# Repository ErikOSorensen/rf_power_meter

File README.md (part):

# RF Power Meter

Dual-channel RF power meter using Raspberry Pi Pico with W5500 Ethernet, featuring SCPI control and mDNS discovery.

## Architecture Overview

```
┌─────────────────────────────────────────────────────────────────┐
│                         main.py                                  │
│                    (Application Controller)                      │
│  - Initializes all subsystems                                   │
│  - Runs async task scheduler                                    │
│  - Coordinates sensor reading, display, and network tasks       │
└─────────────────────────────────────────────────────────────────┘
         │              │              │              │
         ▼              ▼              ▼              ▼
┌─────────────┐ ┌─────────────┐ ┌─────────────┐ ┌─────────────┐
│   sensors/  │ │  display/   │ │    net/     │ │    scpi/    │
│             │ │             │ │             │ │             │
│ Head ADC,   │ │ 256x64 OLED │ │ Ethernet &  │ │  Command    │
│ temp, EEPROM│ │ both chans  │ │ TCP server  │ │  parsing    │
└─────────────┘ └─────────────┘ └─────────────┘ └─────────────┘
```

## Key Features

- **EEPROM-based calibration**: Each sensor module stores its own calibration data in an onboard EEPROM. Calibration travels with the sensor, not the channel.
- **Frequency-dependent calibration**: Store separate offset/slope corrections for each calibration frequency. Between points the corrections are linearly interpolated.
- **Self-contained sensor heads**: Each head carries its detector, 16-bit ADC, temperature sensor and EEPROM. Only power and I2C travel over the cable.
- **One I2C bus per head**: Each sensor head hangs on its own Pico I2C controller (I2C0 for channel 1, I2C1 for channel 2), so heads are interchangeable and no multiplexer is needed.
- **Hot-swappable sensors**: Sensors are automatically detected at startup and on plug-in via a presence detect line.
- **Single 256x64 grayscale OLED**: An SSD1322 panel over SPI shows both channels, one row each.
- **Front panel encoder**: A rotary encoder with push switch sets the frequency and external attenuator of each channel. SCPI writes override it, and `SYSTem:KLOCk` can lock it out.
- **SCPI control**: Standard SCPI commands over TCP port 5025.
- **mDNS discovery**: Find the meter as `rfmeter.local`.

## Display

The main screen, rendered at 3x by `python3 tests/test_screen.py docs/display_main.png 3`
with the firmware's own layout code (`src/display/layout.py`).

## Repository Layout

| Directory | Contents |
|-----------|----------|
| `src/` | MicroPython firmware. Its contents mirror the Pico's filesystem root: everything in it, and nothing else, is copied to the Pico. |
| `tools/` | Desktop-only Python scripts (font generation, calibration, test utilities). Never copied to the Pico. See `tools/README.md`. `tools/sim/` holds desktop stand-ins for MicroPython modules (`framebuf`, `micropython`). |
| `tests/` | Tests that run both on the Pico (`mpremote run`) and on the desktop. `tests/test_screen.py` renders the display screens to PNG. |
| `docs/` | Images for the documentation, such as the display render above. |
| `hardware/` | KiCad projects and the project-local KiCad library. See `hardware/README.md`. |

### Deploying the Firmware

With [`mpremote`](https://docs.micropython.org/en/latest/reference/mpremote.html):

```
cd src
mpremote cp -r . :
mpremote reset
```

## File Responsibilities

All paths below are relative to `src/`.

### Core

| File | Purpose |
|------|---------|
| `main.py` | Application entry point. Initializes hardware, detects sensors, starts async tasks for sensor reading (50ms), display updates (200ms), TCP server, and mDNS. |
| `config.py` | Central configuration: GPIO pins, I2C buses and addresses, display SPI, encoder, network settings, instrument identity. |

### Sensors (`sensors/`)

| File | Purpose |
|------|---------|
| `ads1115.py` | Low-level driver for the ADS1115 16-bit ADC in each sensor head. Continuous-conversion mode; reads never block. |
| `mcp9808.py` | Driver for the MCP9808 temperature sensor in each sensor head. |
| `eeprom.py` | AT24Cxx EEPROM driver. Reads/writes sensor type, serial number, and calibration data. |
| `calibration.py` | Calibration management. Holds the per-channel I2C buses, detects sensors via EEPROM, manages per-frequency calibration, handles voltage-to-dBm conversion. |
| `power_sensor.py` | High-level power measurement. `PowerChannel` handles per-channel reading and averaging. `PowerMeter` manages both channels. |

### Display (`display/`)

| File | Purpose |
|------|---------|
| `ssd1322.py` | Low-level driver for the SSD1322 256x64 4-bit grayscale OLED (4-wire SPI). Frame buffer is `framebuf.GS4_HMSB`, which matches the controller's RAM layout. |
| `bitmapfont.py` | Draws the generated bitmap fonts in `fonts/` (B612 Bold 30 px, Regular 12 px and 9 px; 4-bit antialiased, tabular digits). Regenerate with `tools/fonts/make_fonts.py`. |
| `layout.py` | Screen layout, hardware-free so it also runs on the desktop. One 32 px row per channel: channel name with sensor type and head temperature, frequency and pad (editable, inverted while editing), the reading in 30 px B612 Bold right-aligned at a fixed position, and the unit. Also the startup (IP address, hostname), error and remote-lock screens. |
| `power_display.py` | `DisplayManager`: owns the panel, reads the meter state and draws it with `layout.py`. Holds the startup screen with the IP address for 3 s after DHCP succeeds. |

### Front Panel (`ui/`)

| File | Purpose |
|------|---------|
| `encoder.py` | Rotary encoder quadrature decoder and push button, interrupt driven. Expects hardware-debounced inputs. |
| `front_panel.py` | Edit-mode state machine: short press cycles CH1 frequency → CH1 attenuator → CH2 frequency → CH2 attenuator → back to measurement; rotation changes the highlighted value; 5 s idle timeout; remote lock. |

### Network (`net/`)

| File | Purpose |
|------|---------|
| `w5500.py` | W5500 Ethernet initialization. Configures SPI, handles DHCP. |
| `tcp_server.py` | Async TCP server on port 5025 (SCPI standard). |
| `mdns.py` | Multicast DNS responder. Announces `rfmeter.local`. |

### SCPI (`scpi/`)

| File | Purpose |
|------|---------|
| `parser.py` | SCPI command parser. Handles short/long form matching. |
| `commands.py` | SCPI command implementations. |

## Hardware Design

### Design Principle: Digital-Only Cable

Each sensor head contains the complete analog signal chain: RF detector,
RC filter and a 16-bit ADS1115 ADC. The head also carries an EEPROM
(identity and calibration) and an MCP9808 temperature sensor next to the
detector, plus its own voltage regulators. The cable to the main unit
carries only an 8V supply rail, I2C and a presence line.

This keeps the detector's millivolt-level output off the cable, so cable
length, connector contact resistance and ground offsets between units no
longer affect the reading.

### System Block Diagram

```
┌──────────────────────────────────┐              ┌──────────────────────────────┐
│ Sensor Head 1                    │              │       Main Unit (Pico)       │
│                                  │              │                              │
│  RF IN   ┌─────────┐  ┌────────┐ │   Ethernet   │     ┌──────────────────┐     │
│  (SMA) ──┤ AD8307  ├─►│ADS1115 ├─┤   cable      │     │       Pico       │     │
│          └─────────┘  │  0x48  │ │ (8V + I2C)   │     │                  │     │
│          ┌─────────┐  └────────┤ │              │     │ I2C0 (GP0/GP1)   │     │
│          │ MCP9808 ├───────────┼─┼══════════════┼─────┤                  │     │
│          │  0x18   │  ┌────────┤ │              │     │ I2C1 (GP2/GP3)   │     │
│          └─────────┘  │ EEPROM │ │              │  ┌──┤                  │     │
│                       │  0x50  │ │              │  │  │ SPI0 (GP16-19)   ├──┐  │
│                       └────────┘ │              │  │  │ SPI1 (GP10/11)   ├┐ │  │
└──────────────────────────────────┘              │  │  └──────────────────┘│ │  │
                                                  │  │                      │ │  │
┌──────────────────────────────────┐              │  │  ┌───────────────┐   │ │  │
│ Sensor Head 2                    │              │  │  │  SSD1322 OLED │◄──┘ │  │
│                                  │              │  │  │  256 x 64     │     │  │
│  RF IN   ┌─────────┐  ┌────────┐ │   Ethernet   │  │  └───────────────┘     │  │
│  (SMA) ──┤ AD8318  ├─►│ADS1115 ├─┤   cable      │  │  ┌───────────────┐     │  │
│          └─────────┘  │  0x48  │ │ (8V + I2C)   │  │  │     W5500     │◄────┘  │
│          ┌─────────┐  └────────┤ │              │  │  │   Ethernet    │        │
│          │ MCP9808 ├───────────┼─┼══════════════┼──┘  └───────────────┘        │
│          │  0x18   │  ┌────────┤ │              │                              │
│          └─────────┘  │ EEPROM │ │              │                              │
│                       │  0x50  │ │              │                              │
│                       └────────┘ │              │                              │
└──────────────────────────────────┘              └──────────────────────────────┘
```

Every head uses the same I2C addresses, so the heads are interchangeable.
The RP2040 has two independent I2C controllers; each one is wired to one
RJ45 jack, so head 1 is always on I2C0 and head 2 on I2C1. Nothing else
shares those buses.

### Ethernet Cable Pinout (T-568B)

Sensors connect to the main unit via standard Ethernet cables. Only power
and digital signals are carried.

Each I2C line shares a twisted pair with its own ground return, which
keeps SDA-to-SCL crosstalk low and gives each signal a tight return path.

| Pin | Pair | Wire Color | Function | Notes |
|-----|------|------------|----------|-------|
| 1 | Orange | Orange/White | V+ (8V) | Head supply from the main unit's LM317, 12V TVS per port |
| 2 | Orange | Orange | GND | Power return |
| 3 | Green | Green/White | I2C SDA | Pico I2C0 (head 1) or I2C1 (head 2) |
| 6 | Green | Green | GND | Return for SDA |
| 4 | Blue | Blue | I2C SCL | Pico I2C0 (head 1) or I2C1 (head 2) |
| 5 | Blue | Blue/White | GND | Return for SCL |
| 7 | Brown | Brown/White | GND | Return for presence detect |
| 8 | Brown | Brown | Presence Detect | Tied to GND in the head; pulled up in the main unit |

**Power Supply Notes:**
- The cable carries a single V+ of 8V, made by an LM317 on the main
  board. Each head still regulates its own 3.3V (and 5V where the
  detector needs it), so cable drop, contact resistance and main-unit
  supply noise do not reach the analog parts.
- The EEPROM, ADS1115 and MCP9808 always run on the head's 3.3V
- 3.3V detectors (AD8307, LTC5582): detector VCC from the head's 3.3V LDO
- 5V detectors (AD8317, AD8318): detector VCC from the head's 5V LDO
- Pins 2, 5, 6 and 7 are all GND and tied together at both ends; no
  conductor in the cable floats

**Hot-Swap Detection:**
- Pin 8 is tied to GND in each sensor head
- Main unit pulls each presence detect GPIO up to 3.3V (10kΩ, plus the
  RP2040 internal pull-up)
- When sensor is connected: GPIO reads LOW
- When sensor is disconnected: GPIO reads HIGH
- Either edge triggers sensor re-detection, which also re-configures the
  head's ADC (it powers up in single-shot mode)
- A ground tie needs no working rail in the head, so a head with a dead
  regulator still registers as present and can be reported as faulty

### I2C Topology

The main unit has no I2C devices of its own. Each of the Pico's two
I2C controllers runs straight to one RJ45 jack:

| Pico bus | Pins | Goes to |
|----------|------|---------|
| I2C0 | GP0 (SDA), GP1 (SCL) | RJ45 #1, sensor head 1 |
| I2C1 | GP2 (SDA), GP3 (SCL) | RJ45 #2, sensor head 2 |

**Sensor head bus (identical in every head):**

| Device | Address | Function |
|--------|---------|----------|
| ADS1115 | 0x48 | ADC for detector output (ADDR → GND) |
| MCP9808 | 0x18 | Temperature next to the detector (A0-A2 → GND) |
| AT24CS04 | 0x50 (0x51 upper half, 0x58 factory serial) | Sensor type, serial number, calibration |

Because the heads never share a bus, there is no multiplexer and no
channel-select transaction. A fault on one cable (a head yanked
mid-transfer, a shorted SDA) can only hang that channel's bus; the other
channel and the display are unaffected.

**Why One ADS1115 Per Head?**

1. **No analog on the cable**: The detector output is digitised within a
   few centimetres of the detector.
2. **Interchangeable heads**: Every head looks the same to the main unit.
   Calibration, identity and ADC travel together.
3. **Independent sampling**: Both ADCs free-run in continuous mode at
   128 SPS on separate buses. The Pico just reads the latest conversion
   from each head, so reads do not block and the two channels are
   sampled within a millisecond of each other.
4. **Spare inputs**: AIN2/AIN3 (grounded on the AD8307 head) are available for future heads with two
   detectors (e.g. a directional coupler head reporting forward and
   reflected power).

**Why a Temperature Sensor in the Head?**

Logarithmic detectors drift with temperature (AD8307: roughly ±0.3 dB
over -40 to +85 °C, AD8318 somewhat more). Measuring the temperature
at the detector allows this drift to be characterised per head and
compensated in firmware. The reading is available via
`MEASure:TEMPerature[1|2]?`. Temperature compensation coefficients are
not yet stored in the EEPROM format (see format version in `src/sensors/eeprom.py`).

### Pico Pin Assignments

| Function | Pico Pin | Notes |
|----------|----------|-------|
| Head 1 I2C SDA | GP0 | I2C0 → RJ45 #1 pin 3 |
| Head 1 I2C SCL | GP1 | I2C0 → RJ45 #1 pin 4 |
| Head 2 I2C SDA | GP2 | I2C1 → RJ45 #2 pin 3 |
| Head 2 I2C SCL | GP3 | I2C1 → RJ45 #2 pin 4 |
| Sensor 1 Detect | GP4 | Pull-up, active low, IRQ on edge |
| Sensor 2 Detect | GP5 | Pull-up, active low, IRQ on edge |
| Encoder A | GP6 | Via RC filter + 74HC14, IRQ on edge |
| Encoder B | GP7 | Via RC filter + 74HC14, IRQ on edge |
| Encoder Switch | GP8 | Via RC filter + 74HC14, high = pressed |
| Display SPI SCK | GP10 | SPI1 |
| Display SPI MOSI | GP11 | SPI1 TX (SSD1322 is write-only) |
| Display CS | GP13 | Active low |
| Display D/C | GP14 | High = data, low = command |
| Display RST | GP15 | Active low |
| W5500 SPI MISO | GP16 | SPI0 |
| W5500 CS | GP17 | |
| W5500 SPI SCK | GP18 | SPI0 |
| W5500 SPI MOSI | GP19 | SPI0 |
| W5500 RST | GP20 | |
| W5500 INT | GP21 | Not used by the firmware |

The controller is a W5500-EVB-Pico, so the W5500 and its SPI wiring
(GP16-GP21) are on the module itself. GP9, GP12, GP22 and GP26-GP28 are
free (extra buttons, status LED).

### Sensor Head Schematic

Each sensor head contains an RF detector, an ADS1115 ADC, an MCP9808
temperature sensor, an EEPROM and its own voltage regulation. The cable
delivers 8V; the head makes a 3.3V rail for the digital parts and, for
5V detectors, a 5V rail as well.

```
                 ┌──────────────────────────────────────────────────────────────────┐
                 │                          Sensor Head                             │
   RJ45          │                                                                  │
  ┌─────┐        │  ┌─────┐  ┌───────────┐   5V (detector)   ┌───────────┐          │
  │1 V+ ├────────┼──┤ TVS ├──┤ 5V LDO    ├───────────────────┤ 3.3V LDO  ├──┬─ 3V3  │
  │2 GND├────────┼┐ │10µF │  │ 5V heads  │                   │           │  │       │
  │3 SDA├────┐   ││ └─────┘  └───────────┘                   └───────────┘  │       │
  │6 GND├────┼───┼┤     (3.3V heads: V+ feeds the 3.3V LDO directly)        │       │
  │4 SCL├────┼─┐ ││                                                         │       │
  │5 GND├────┼─┼─┼┤                                                         │       │
  │7 GND├────┼─┼─┼┤   ┌──────────┐  ┌──────────┐     ┌──────────┐           │       │
  │8 DET├─┐  │ │ ││   │ ADS1115  │  │ MCP9808  │     │ EEPROM   │           │       │
  └─────┘ │  │ │ ││   │  0x48    ├──┤  0x18    ├─────┤  0x50    ├───────────┘       │
         GND │ │ ││   │ SDA  SCL │  │ SDA  SCL │     │ SDA  SCL │  (all on 3V3)     │
             │ │ ││   └──┬────┬──┘  └──┬────┬──┘     └──┬────┬──┘                   │
             └─┼─┼┼──────┴────┼────────┴────┼───────────┴────┼──── SDA  [4.7k → 3V3] │
               └─┼┼───────────┴─────────────┴────────────────┴──── SCL  [4.7k → 3V3] │
                 ││                                                                  │
                 ││   ADS1115 AIN0 ◄──────────┬── OUT  ┌─────────────┐              │
                 ││                        [100nF]     │ RF Detector │              │
                 ││   ADS1115 AIN1 ◄──────────┴── COM  │   AD8307    ├─[3dB pad]─ SMA│
                 ││                                    │ VCC ◄───────┼── 3V3 or 5V   │
                 │└─ GND                               └─────────────┘   rail        │
                 │                                                                  │
                 │   ADS1115: ADDR → GND, ALERT/RDY → 10kΩ pull-up, AIN2/AIN3 → GND  │
                 └──────────────────────────────────────────────────────────────────┘
```

**Component List (per sensor head):**
- RF detector IC (AD8307, AD8317, AD8318, LTC5582, etc.)
- ADS1115 16-bit ADC (TSSOP-10), ADDR → GND
- MCP9808 temperature sensor (MSOP-8), A0-A2 → GND, placed as close to the detector as layout allows
- AT24CS04-SSHM EEPROM, SOIC-8 (I2C address 0x50, factory serial number at 0x58; A1, A2 and WP → GND)
- 3.3V low-noise LDO LP2985-33 (SOT-23-5, 16V input; MIC5205-3.3 is a drop-in alternative) for ADC, temperature sensor, EEPROM and 3.3V detectors
- 5V LDO (e.g. AP7361C-50 or LD1117S50, SOT-223) on 5V-detector heads only; the 3.3V LDO then cascades from the 5V rail
- Power input: 10µF/25V tantalum + 12V TVS (SMF12A) on V+; LP2985 with 1µF at VIN, 10nF on BYPASS and 10µF tantalum at VOUT
- RJ45 jack: Würth 615108150221R mid-mount (shielded, tab down, no magnetics, no LEDs; project library `rf_power_meter:RJ45_WE-615108150221R`), sits in a board-edge cutout to fit the enclosure height; pin 8 tied to GND for presence detect
- SMA connector for RF input: Amphenol RF 132289, edge mount (project library `rf_power_meter:SMA_132289`)
- 3 dB pi attenuator between SMA and detector: 17.6Ω series, 2× 294Ω shunt, thin-film 1% (see `hardware/README.md`)
- Detector output filter: 100nF from OUT to ground, straight into ADS1115 AIN0 (the AD8307 output is 12.5kΩ, no series resistor needed)
- Detector input network: 52.3Ω termination, 2× 10nF C0G coupling capacitors on INP and INM (see `hardware/README.md`)
- Decoupling capacitors (100nF on each IC supply pin)
- I2C pull-up resistors (2× 4.7kΩ to the head's 3V3)
- 10kΩ pull-up on ADS1115 ALERT/RDY (unused, keeps the open-drain output defined)
- ESD protection (1× ESDAVLC6-2BLY for I2C lines)
- RF detector support components (per datasheet)

**Board markings:** the head PCB silkscreen carries the I2C address
table (ADS1115 0x48, MCP9808 0x18, AT24CS04 0x50 lower / 0x51 upper) and
the head label on the top side, and the RJ45 pinout on the bottom side,
so a head can be checked on the bench without this document.

**Test points:** six beaded wire loops (TestPoint_Loop_D1.80mm, 1.0 mm
hole) for bench checks: TP1 detector output (AD8307 OUT / ADS1115
AIN0), TP2 +3V3, TP3 VCC (the 8 V from the cable), TP4 SDA, TP5 SCL,
TP6 GND. Clip a scope ground to TP6 and the detector output can be
watched live while the ADC reads it.

**Detector Supply Voltage Reference:**

| Sensor | Supply | Head rail for detector | Max output | Fits ADS1115 at 3.3V? |
|--------|--------|------------------------|------------|------------------------|
| AD8307 | 2.7V - 5.5V | 3.3V (5V optional) | ~2.5V | Yes |
| AD8317 | 3.0V - 5.5V | 5V recommended | ~2.1V | Yes |
| AD8318 | 4.5V - 5.5V | 5V required | ~2.1V | Yes |
| LTC5582 | 3.0V - 3.6V | 3.3V only | ~2.1V | Yes |

The ADS1115 runs from 3.3V in all heads. Its inputs must stay below
VDD + 0.3V, which every listed detector satisfies even when powered from 5V.
The PGA is set to ±4.096V (125 µV/LSB); for a detector with a 25 mV/dB
slope that is 0.005 dB per count.

### Main Unit Schematic

The main unit takes 12V DC from a 1A adapter. Three regulators make the
rails: an LM317 (SOT-223) set to 8V for the two RJ45 ports (12V TVS per port), a 5V
buck module for the W5500-EVB-Pico, whose own 3.3V regulator powers the
RP2040 and the W5500, and a small 3.3V LDO for the OLED module. With the
analog chain moved to the heads, the main unit is purely digital.

```
  12V DC ───┬──► LM317 (8V) ──────────────────────────────────► To RJ45 Pin 1 (V+)
            │                                                     via 12V TVS per port
            ├──► 5V buck module ───────┬──► Pico VSYS (RP2040 + W5500)
            │                          └──► 3.3V LDO ──► OLED module
            │
            │    Raspberry Pi Pico
            │   ┌─────────────────┐
            │   │ GP0 (I2C0 SDA)  ├──[10kΩ to 3V3]──► RJ45 #1 pin 3 (SDA)
            │   │ GP1 (I2C0 SCL)  ├──[10kΩ to 3V3]──► RJ45 #1 pin 4 (SCL)
            │   │ GP2 (I2C1 SDA)  ├──[10kΩ to 3V3]──► RJ45 #2 pin 3 (SDA)
            │   │ GP3 (I2C1 SCL)  ├──[10kΩ to 3V3]──► RJ45 #2 pin 4 (SCL)
            │   │ GP4 (DET1)      ├◄─[10kΩ to 3V3]─── RJ45 #1 pin 8 (low = present)
            │   │ GP5 (DET2)      ├◄─[10kΩ to 3V3]─── RJ45 #2 pin 8 (low = present)
            │   │                 │
            │   │ GP10 (SPI1 SCK) ├────────┐
            │   │ GP11 (SPI1 TX)  ├───────┐│
            │   │ GP13 (CS)       ├──────┐││
            │   │ GP14 (D/C)      ├─────┐│││
            │   │ GP15 (RST)      ├────┐││││       ┌──────────────────────┐
            │   │                 │    │││││       │   SSD1322 OLED       │
            │   │                 │    ││││└───────┤ SCLK      256 x 64   │
            │   │                 │    │││└────────┤ SDIN                 │
            │   │                 │    ││└─────────┤ CS#                  │
            │   │                 │    │└──────────┤ D/C#                 │
            │   │                 │    └───────────┤ RES#                 │
            │   │                 │                │ VDD (3.3V)  GND      │
            │   │                 │                └──────────────────────┘
            │   │ GP16 (SPI MISO) ├────────┐
            │   │ GP17 (SPI CS)   ├───────┐│
            │   │ GP18 (SPI SCK)  ├──────┐││
            │   │ GP19 (SPI MOSI) ├─────┐│││
            │   │ GP20 (RST)      ├────┐││││       ┌────────────────┐
            │   │                 │    │││││       │     W5500      │
            │   │                 │    ││││└───────┤ MISO           │
            │   │                 │    │││└────────┤ MOSI           │
            │   │                 │    ││└─────────┤ SCK            │
            │   │                 │    │└──────────┤ CS             │
            │   │                 │    └───────────┤ RST            │
            │   │ VSYS ◄──────────┼──── 5V         │ 3V3        GND │
            │   │ GND             ├──── GND        │            ════╪══► Ethernet
            │   └─────────────────┘                └────────────────┘

                RJ45 Jacks (x2)
                ┌─────────────────────────────────────┐
                │  Sensor 1          Sensor 2         │
                │  ┌───────┐         ┌───────┐        │
   V+ (8V) ─────┼─►│1: V+  │         │1: V+  │◄───────┼─── V+ (8V)
   GND ─────────┼─►│2: GND │         │2: GND │◄───────┼─── GND
   GP0 (SDA0) ──┼─►│3: SDA │         │3: SDA │◄───────┼─── GP2 (SDA1)
   GP1 (SCL0) ──┼─►│4: SCL │         │4: SCL │◄───────┼─── GP3 (SCL1)
   GND ─────────┼─►│5: GND │         │5: GND │◄───────┼─── GND
   GND ─────────┼─►│6: GND │         │6: GND │◄───────┼─── GND
   GND ─────────┼─►│7: GND │         │7: GND │◄───────┼─── GND
   GP4 (DET1) ──┼──│8: DET │         │8: DET │────────┼─── GP5 (DET2)
                │  └───────┘         └───────┘        │
                └─────────────────────────────────────┘
```

**Display:**
- SSD1322 controller, 256x64 pixels, 4-bit grayscale (16 levels)
- 4-wire SPI at up to 10 MHz on the Pico's SPI1; the controller is
  write-only, so MISO is not connected
- 3.3V logic (VDDIO 1.65-3.5V), so no level shifting
- Connected through a 16-way IDC ribbon from the 2x8 header J1; pinout
  in `hardware/README.md`
- A full frame is 8 KB; at 10 MHz a refresh takes about 7 ms. The
  firmware redraws at 5 Hz
- Both channels share the panel: channel 1 on the top row, channel 2
  on the bottom row. The IP address and mDNS name are on the startup
  screen, which stays up for 3 s after DHCP succeeds

**Power Supply Requirements:**
- 12V DC input from a 1A AC/DC adapter on a 2-pole screw terminal,
  reverse-polarity protected by a series SS14 Schottky
- An LM317 (SOT-223) set to 8V with R1 = 240Ω, R2 = 1.3kΩ makes the
  head rail. It dissipates under 0.7W with two AD8318 heads and needs
  only a copper pour
- The 8V rail goes to each RJ45 pin 1 with a 12V TVS. The per-port
  resettable fuses that would isolate a shorted cable are not fitted in
  the current schematic
- A 1A 5V buck module (Recom R-78C5.0-1.0, 78xx pinout) feeds Pico VSYS
  through an SS14 Schottky, so USB can be connected at the same time
- On the W5500-EVB-Pico the W5500 shares the module's 3.3V regulator
  with the RP2040, so it is covered by the 5V feed to VSYS
- A separate AP7361C-33 LDO (SOT-223) from the 5V rail supplies the OLED
  module. A 256x64 OLED module with its onboard
  panel-voltage boost can draw 100-200 mA at full brightness, and the
  Pico's 3V3 pin is already carrying the W5500. Skip the LDO if the
  module accepts 5V on its own regulator input
- Each head draws roughly 1 mA of digital current plus the detector's
  supply (AD8307 ~8 mA, AD8317 ~22 mA, AD8318 ~68 mA)
- Typical total input current: ~250mA at 12V (depends on detectors,
  display content and Ethernet activity); the 1A adapter has ample margin

## Front Panel Operation

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
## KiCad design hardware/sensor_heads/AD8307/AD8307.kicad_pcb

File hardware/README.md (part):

# Hardware Design

KiCad project files for the RF Power Meter.

## Directory Structure

- `main_board/` - Main unit PCB: Pico, W5500, SSD1322 OLED header, encoder debounce, RJ45 jacks
- `sensor_heads/AD8307/` - AD8307 sensor head (detector + ADC + temperature sensor + EEPROM). Template for other heads.
- `lib/` - Project-local KiCad library (symbols, footprints, 3D models). See `lib/README.md`.

## Design Notes

See the main [README.md](../README.md) for:
- System block diagram
- Ethernet cable pinout (T-568B)
- I2C topology and addresses
- Pico pin assignments
- Sensor head schematic and component list

The cable between main unit and head carries only power and I2C. All
analog conditioning lives in the sensor head.

## Sensor Head: Power

The cable delivers V+ = 8V on RJ45 pin 1 (from the LM317 on the main
board, see below). Every head regulates locally anyway, so the analog
parts never see the cable:

```
                 ┌──────────┐
RJ45 pin 1 ──┬───┤ 5V LDO   ├──┬──── 5V: detector (5V heads only)
   (V+)      │   │ SOT-223  │  │
          [10µF] └──────────┘  │   ┌──────────┐
             │                 └───┤ 3.3V LDO ├──┬──── 3V3: ADS1115, MCP9808,
          [TVS 12V]                │ SOT-23-5 │  │           EEPROM, pull-ups,
             │                     └──────────┘ [10µF]       3.3V detector
            GND                                  │
                                                GND
```

- **3.3V LDO: LP2985-33 (SOT-23-5).** Low-noise, 16V input, 150mA. This
  rail feeds the ADC, so noise matters more than efficiency; a buck
  converter is not appropriate here. Capacitors per the datasheet, all
  ceramic (the current LP2985 is stable with ceramics, ESR window ≈ 5mΩ
  to 3Ω):

  | Pin | Capacitor | Notes |
  |-----|-----------|-------|
  | VIN | 1µF, 25V X7R (C9) | Right at the pin. The 10µF/TVS at the RJ45 is the bulk; if it sits within ~1cm of the regulator it can serve as the input capacitor alone. |
  | VOUT | 10µF/25V tantalum (C11, as drawn) or 10µF 10V X7R | Datasheet minimum is 2.2µF; 10µF stiffens the rail against the AD8307's signal-dependent supply current. Up to 100µF is allowed. |
  | BYPASS | 10nF C0G (C10) | Cuts bandgap noise by ~10×. Slows start-up to a few ms, which is irrelevant here. |
  | ON/OFF | tie to VIN | Must not float. |

  MIC5205-3.3 is a pin-compatible fallback with the same capacitor
  values.
- **5V LDO (5V-detector heads only):** AP7361C-50 or LD1117S50 in SOT-223.
  The 3.3V LDO then takes its input from the 5V rail, so the hot part is
  the SOT-223 and the 3.3V regulator sees only ~1.7V across it.
- **3.3V-detector heads:** omit the 5V LDO, feed the 3.3V LDO from V+.
- **Input protection:** 10µF/25V tantalum (C8; a 25V X7R ceramic also works) and a
  12V TVS (SMF12A, D2) on V+ at the RJ45. The RJ45 is keyed, so reverse polarity
  protection is optional; a Schottky in series costs 0.3V of headroom if
  wanted.
- **Outputs:** 10µF on the 3.3V LDO output (see above), 10µF on the 5V
  LDO output, plus 100nF at every IC.

**Dissipation at 8V input:**

| Head | Regulator | Current | Drop | Power | Package |
|------|-----------|---------|------|-------|---------|
| AD8307 (3.3V) | 3.3V LDO | ~10mA | 4.7V | ~50mW | SOT-23-5, fine |
| AD8318 (5V) | 5V LDO | ~70mA | 3V | ~210mW | SOT-223 (~60°C/W), ~13°C rise |
| AD8318 (5V) | 3.3V LDO | ~2mA | 1.7V | ~3mW | SOT-23-5, fine |

Allowing for cable drop and LM317 tolerance the 5V LDO still has well
over 2V of headroom, more than the 1.1V dropout of an LD1117 at this
current. The 12V TVS on V+ stays: its 12V standoff is comfortably above
the 8V rail.

## Sensor Head: Detector to ADC

The detector output drives the ADS1115 differential input directly, with
one filter capacitor, all on the head PCB:

```
AD8307 OUT ─────────────┬─── ADS1115 AIN0
                        │
                     [100nF]
                        │
AD8307 COM ─────────────┴─── ADS1115 AIN1 (and GND)
```

- **No series resistor.** The AD8307 OUT pin is a current output
  (2 µA/dB) into an internal 12.5kΩ resistor, so its source impedance is
  already 12.5kΩ. A series resistor adds nothing; the capacitor alone
  presents the ADS1115 sampling switch with a low impedance.
- **C: 100nF** against the 12.5kΩ source gives a corner near 130Hz
  (τ ≈ 1.3ms). That is the detector's "video bandwidth", the standard
  way of filtering a log amp output, and it removes detector ripple and
  RF pickup well before the ADC. For a meter sampled at 20Hz it is
  comfortably fast; shrink the capacitor if a faster response is ever
  wanted (10nF ≈ 1.3kHz).
- **Differential input**: AIN1 ties to the detector's ground pin so the
  ADC measures the detector output relative to its own reference, not
  relative to wherever the ADC ground happens to be on the PCB. Keep the
  AIN1 trace short.
- No TVS is needed on the analog path; it never leaves the board.

No amplification is needed: detector outputs (0.2V to 2.5V typical) are
well-matched to the ADS1115 at the ±4.096V PGA setting, giving ~20,000
counts across the signal range.

## Sensor Head: ADS1115 Configuration

| Pin | Connection |
|-----|------------|
| VDD | Head 3.3V rail, 100nF decoupling |
| ADDR | GND → I2C address 0x48 (same in every head) |
| ALERT/RDY | 10kΩ pull-up to 3.3V, otherwise unconnected |
| AIN0 | Detector output (100nF to ground at the pin) |
| AIN1 | Detector ground |
| AIN2, AIN3 | GND (unused inputs tied low; a two-detector head would free them) |

The firmware puts the ADC in continuous conversion mode (128 SPS, AIN0-AIN1,
±4.096V) when the head is detected and then just reads the conversion
register. The ADS1115 powers up in single-shot mode, so this is redone on
every hot-plug.

## Sensor Head: MCP9808 Temperature Sensor

| Pin | Connection |
|-----|------------|
| VDD | Head 3.3V rail, 100nF decoupling |
| A0, A1, A2 | GND → I2C address 0x18 |
| ALERT | Unconnected (open-drain, unused) |

Place the MCP9808 as close to the detector IC as possible, on the same
side of the board, with a solid ground pour connecting the two. The point
is to track the detector's temperature, not the ambient. Default
resolution (0.0625°C) is used.

## Sensor Head: EEPROM

AT24CS04-SSHM (SOIC-8, 4 kbit, with a factory 128-bit serial number).
A1 and A2 are tied to GND for address 0x50 (0x51 answers for the upper
256 bytes; the serial number block answers at 0x58, word addresses
0x80-0x8F). Do not leave the address pins floating: they have no
internal pull-downs. WP (pin 7) is tied to GND, write enabled, since
calibration is saved from the SCPI interface. Pin 1 (NC) is left open.
The UDFN variant (AT24CS04-MAHM) has the same pinout plus an exposed
pad, which may be grounded or left floating.

## Sensor Head: RF Input

Amphenol RF 132289 SMA jack, PCB edge mount, 50Ω. Symbol
`rf_power_meter:SMA_132289` and footprint
`rf_power_meter:SMA_Amphenol_132289_EdgeMount` in the project library
(`lib/`). The footprint carries the STEP model. Place the connector on a
board edge with the pad and detector input network directly behind it;
keep the 50Ω trace to the detector short.

### 3 dB Input Pad

A 3 dB pi attenuator sits between the SMA and the detector input network:

```
SMA ──┬──[17.6Ω]──┬──── to 52.3Ω termination / coupling caps / detector
      │           │
   [294Ω]      [294Ω]
      │           │
     GND         GND
```

| Position | Ideal | Chosen value | Resulting attenuation |
|----------|-------|-----------|------------------------|
| Series | 17.61Ω | 17.6Ω (R2 as drawn, E192; 17.4Ω E96 is equally fine) | 3.0 dB, return loss > 30 dB |
| Shunt (×2) | 292.4Ω | 294Ω | |

- **Why:** The pad presents the SMA with a stable 50Ω regardless of the
  detector's input impedance (the AD8307 is ~1.1kΩ with some reactance,
  and the 52.3Ω termination alone gives a mediocre match at the top of the
  band). It also raises the head's maximum input from +17 dBm to
  +20 dBm and takes the first hit from an overload or ESD event.
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
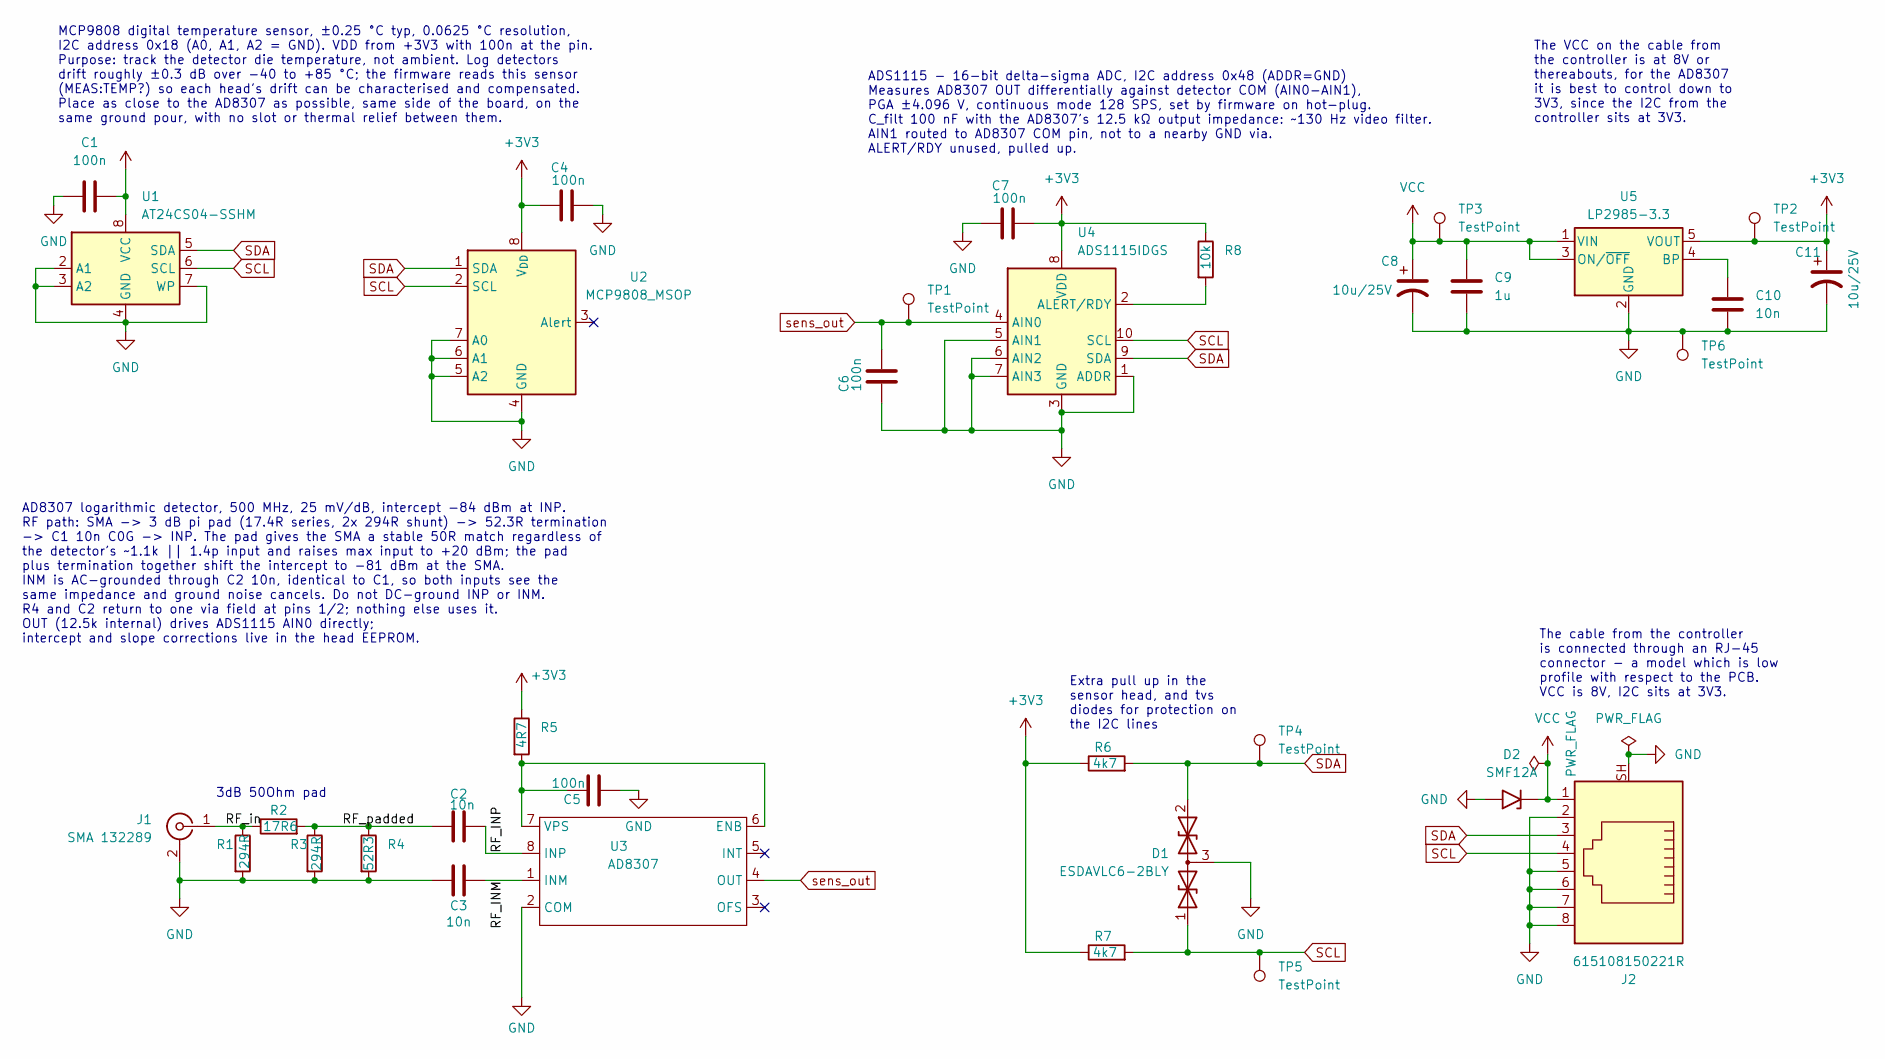
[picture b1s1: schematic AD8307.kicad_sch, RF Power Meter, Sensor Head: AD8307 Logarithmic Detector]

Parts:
C1, C4, C5, C6, C7: 100n; C_0805_2012Metric
C2, C3: 10n; C_0603_1608Metric
C8, C11: 10u/25V; CP_EIA-3528-21_Kemet-B
C9: 1u; C_0805_2012Metric
C10: 10n; C_0805_2012Metric
D1: ESDAVLC6-2BLY; TSOT-23
D2: SMF12A; D_SMF
J1: SMA 132289; SMA_Amphenol_132289_EdgeMount
J2: 615108150221R; RJ45_Wuerth_615108150221R_MidMount
R1, R3: 294R; R_0603_1608Metric
R2: 17R6; R_0603_1608Metric
R4: 52R3; R_0603_1608Metric
R5: 4R7; R_0805_2012Metric
R6, R7: 4k7; R_0805_2012Metric
R8: 10k; R_0805_2012Metric
TP1, TP2, TP3, TP4, TP5, TP6: TestPoint; TestPoint_Loop_D1.80mm_Drill1.0mm_Beaded
U1: AT24CS04-SSHM; SOIC-8_3.9x4.9mm_P1.27mm
U2: MCP9808_MSOP; MSOP-8_3x3mm_P0.65mm
U3: AD8307; SOIC-8_3.9x4.9mm_P1.27mm
U4: ADS1115IDGS; TSSOP-10_3x3mm_P0.5mm
U5: LP2985-3.3; SOT-23-5

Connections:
+3V3: C1.2, C4.1, C7.2, C11.1, R5.1, R6.1, R7.1, R8.1, TP2.1 (1_1), U1.8 (VCC), U2.8 (V_{DD}), U4.8 (VDD), U5.5 (VOUT)
/RF_INM: C3.2, U3.1 (INM)
/RF_INP: C2.2, U3.8 (INP)
/RF_in: J1.1 (In), R1.1, R2.1
/RF_padded: C2.1, R2.2, R3.1, R4.1
GND: C1.1, C3.1, C4.2, C5.2, C6.1, C7.1, C8.2, C9.2, C10.2, C11.2, D1.3 (common), D2.2 (A2), J1.2 (Ext), J2.2, J2.5, J2.6, J2.7, J2.8, J2.SH, R1.2, R3.2, R4.2, TP6.1 (1_1), U1.2 (A1), U1.3 (A2), U1.4 (GND), U1.7 (WP), U2.4 (GND), U2.5 (A2), U2.6 (A1), U2.7 (A0), U3.2 (COM), U4.1 (ADDR), U4.3 (GND), U4.5 (AIN1), U4.6 (AIN2), U4.7 (AIN3), U5.2 (GND)
unnamed: C5.1, R5.2, U3.6 (ENB), U3.7 (VPS)
unnamed: R8.2, U4.2 (ALERT/RDY)
unnamed: C10.1, U5.4 (BP)
SCL: D1.1 (A1), J2.4, R7.2, TP5.1 (1_1), U1.6 (SCL), U2.2 (SCL), U4.10 (SCL)
SDA: D1.2 (A2), J2.3, R6.2, TP4.1 (1_1), U1.5 (SDA), U2.1 (SDA), U4.9 (SDA)
VCC: C8.1, C9.1, D2.1 (A1), J2.1, TP3.1 (1_1), U5.1 (VIN), U5.3 (ON/~OFF)
sens_out: C6.2, TP1.1 (1_1), U3.4 (OUT), U4.4 (AIN0)

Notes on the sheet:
The cable from the controller is connected through an RJ-45 connector - a model which is low profile with respect to the PCB. VCC is 8V, I2C sits at 3V3.
3dB 50Ohm pad
ADS1115 - 16-bit delta-sigma ADC, I2C address 0x48 (ADDR=GND) Measures AD8307 OUT differentially against detector COM (AIN0-AIN1), PGA ±4.096 V, continuous mode 128 SPS, set by firmware on hot-plug. C_filt 100 nF with the AD8307's 12.5 kΩ output impedance: ~130 Hz video filter. AIN1 routed to AD830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
MCP9808 digital temperature sensor, ±0.25 °C typ, 0.0625 °C resolution, I2C address 0x18 (A0, A1, A2 = GND). VDD from +3V3 with 100n at the pin. Purpose: track the detector die temperature, not ambient. Log detectors drift roughly ±0.3 dB over -40 to +85 °C; the firmware reads this sensor (MEAS:TEM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
The VCC on the cable from the controller is at 8V or thereabouts, for the AD8307 it is best to control down to 3V3, since the I2C from the controller sits at 3V3.
AD8307 logarithmic detector, 500 MHz, 25 mV/dB, intercept -84 dBm at INP. RF path: SMA -> 3 dB pi pad (17.4R series, 2x 294R shunt) -> 52.3R termination -> C1 10n C0G -> INP. The pad gives the SMA a stable 50R match regardless of the detector's ~1.1k || 1.4p input and raises max input to +20 dBm; t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
Extra pull up in the sensor head, and tvs diodes for protection on the I2C lines

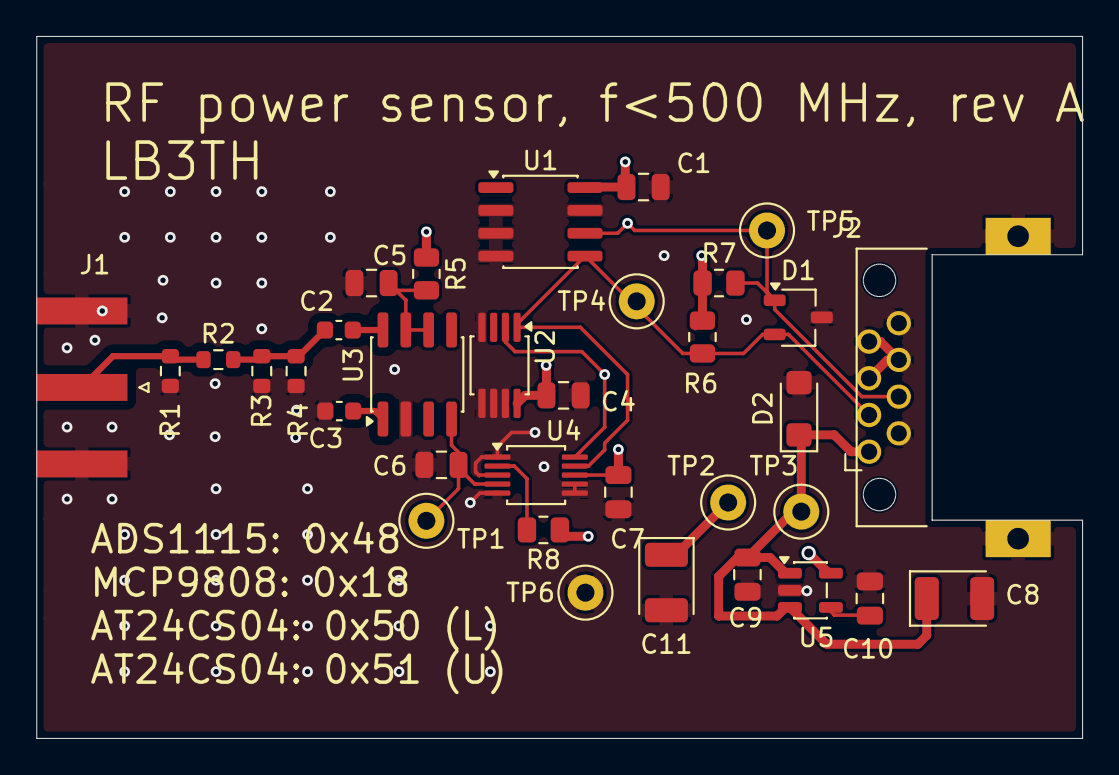
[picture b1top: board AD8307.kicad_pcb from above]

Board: 4 copper layers, 58.1 x 39.0 mm, 34 parts (0 on the bottom side), 13 nets.

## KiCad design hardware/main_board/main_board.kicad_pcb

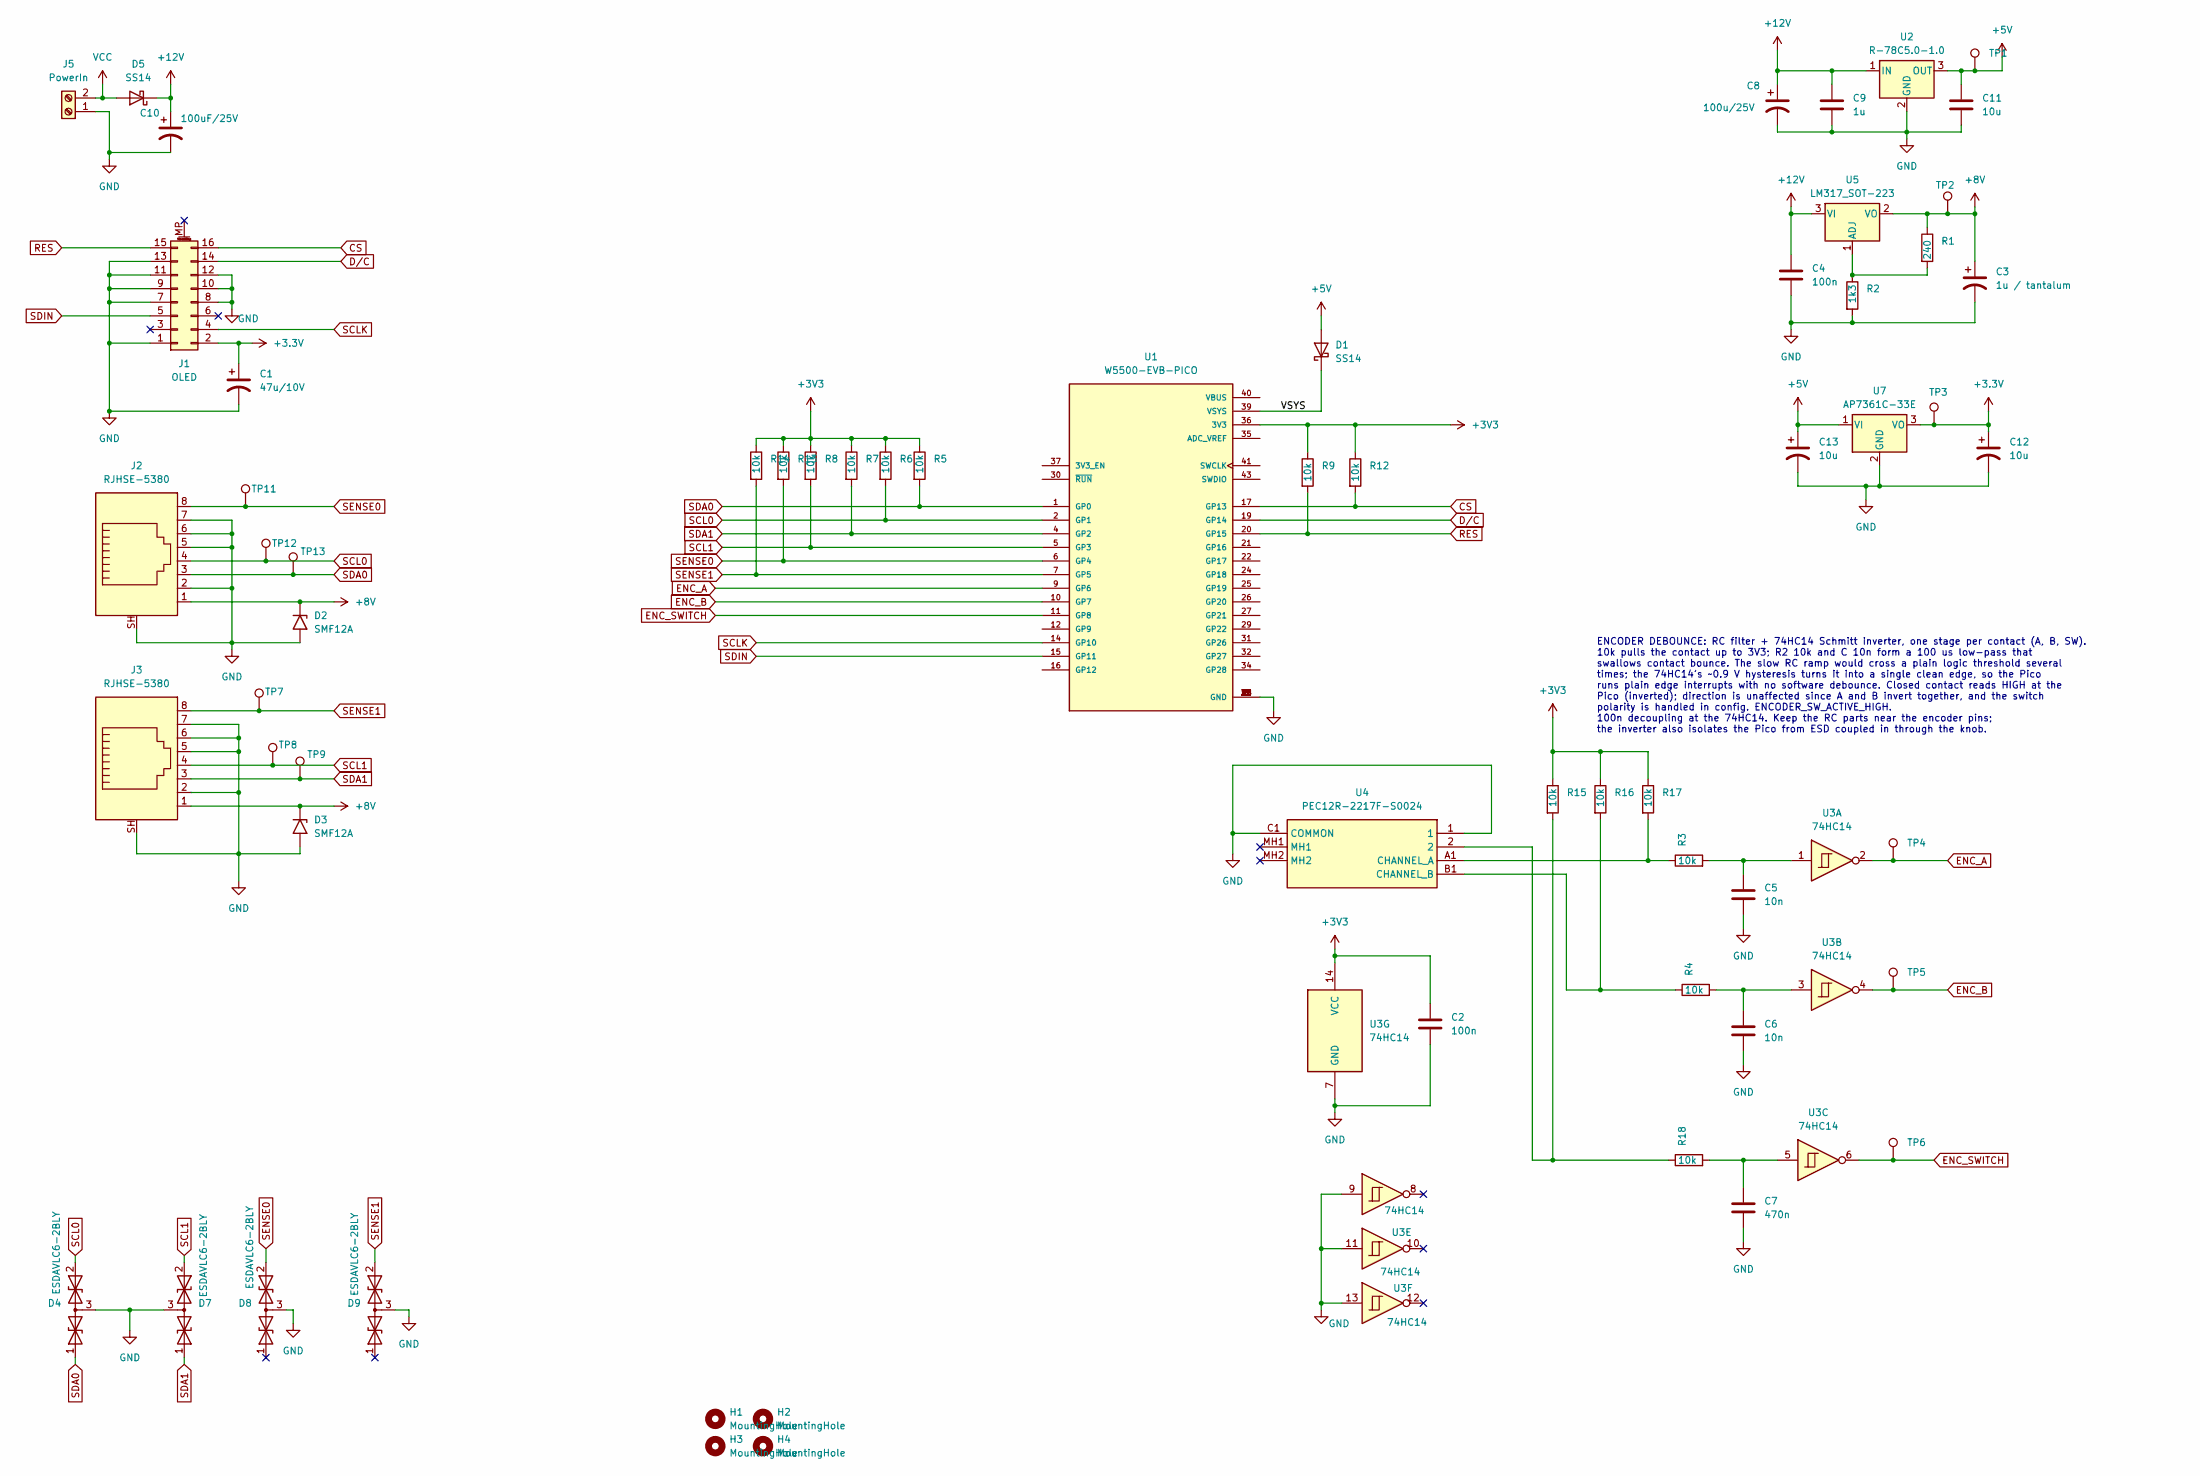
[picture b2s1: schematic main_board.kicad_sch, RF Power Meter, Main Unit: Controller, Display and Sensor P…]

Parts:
C1: 47u/10V; CP_EIA-6032-28_Kemet-C
C2, C4: 100n; C_0805_2012Metric
C3: 1u / tantalum; CP_EIA-2012-15_AVX-P
C5, C6: 10n; C_0805_2012Metric
C7: 470n; C_0805_2012Metric
C8: 100u/25V; CP_Elec_6.3x5.9
C9: 1u; CP_EIA-2012-15_AVX-P
C10: 100uF/25V; CP_Elec_6.3x5.9
C11, C12, C13: 10u; CP_EIA-3528-21_Kemet-B
D1, D5: SS14; D_SMA
D2, D3: SMF12A; D_SMF
D4, D7, D8, D9: ESDAVLC6-2BLY; TSOT-23
H1, H2, H3, H4: MountingHole; MountingHole_3.2mm_M3_ISO7380
J1: OLED; IDC-Header_2x08_P2.54mm_Vertical
J2, J3: RJHSE-5380; RJ45_Amphenol_RJHSE5380; MPN RJHSE-5380
J5: PowerIn; TerminalBlock_Phoenix_MKDS-1,5-2-5.08_1x02_P5.08mm_Horizont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
R1: 240; R_0805_2012Metric
R2: 1k3; R_0805_2012Metric
R3, R4, R5, R6, R7, R8, R9, R12, R13, R14, R15, R16, R17, R18: 10k; R_0805_2012Metric
TP1, TP2, TP3, TP4, TP5, TP6, TP7, TP8, TP9, TP13: TestPoint; TestPoint_Loop_D1.80mm_Drill1.0mm_Beaded
TP11, TP12: TestPoint_Loop_D1.80mm_Drill1.0mm_Beaded
U1: W5500-EVB-PICO; W5500-EVB-Pico_Socketed; PARTREV 2022-01-28
U2: R-78C5.0-1.0; Converter_DCDC_RECOM_R-78E-0.5_THT
U3: 74HC14; SOIC-14_3.9x8.7mm_P1.27mm
U4: PEC12R-2217F-S0024; PEC12R2217FS0024; Mouser Part Number 652-PEC12R-2217F-S24
U5: LM317_SOT-223; SOT-223-3_TabPin2
U7: AP7361C-33E; SOT-223-3_TabPin2

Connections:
+3.3V: C1.1, C12.1, J1.2, TP3.1 (1_1), U7.3 (VO)
+3V3: C2.1, R5.1, R6.1, R7.1, R8.1, R9.1, R12.1, R13.1, R14.1, R15.1, R16.1, R17.1, U1.36 (3V3), U3.14 (VCC)
+5V: C11.1, C13.1, D1.2 (A), TP1.1 (1_1), U2.3 (OUT), U7.1 (VI)
+8V: C3.1, D2.1 (A1), D3.1 (A1), J2.1, J3.1, R1.1, TP2.1 (1_1), U5.2 (VO)
+12V: C4.1, C8.1, C9.1, C10.1, D5.1 (K), U2.1 (IN), U5.3 (VI)
/VSYS: D1.1 (K), U1.39 (VSYS)
CS: J1.16, R12.2, U1.17 (GP13)
D/C: J1.14, U1.19 (GP14)
ENC_A: TP4.1 (1_1), U1.9 (GP6), U3.2
ENC_B: TP5.1 (1_1), U1.10 (GP7), U3.4
ENC_SWITCH: TP6.1 (1_1), U1.11 (GP8), U3.6
GND: C1.2, C2.2, C3.2, C4.2, C5.2, C6.2, C7.2, C8.2, C9.2, C10.2, C11.2, C12.2, C13.2, D2.2 (A2), D3.2 (A2), D4.3 (common), D7.3 (common), D8.3 (common), D9.3 (common), J1.1, J1.7, J1.8, J1.9, J1.10, J1.11, J1.12, J1.13, J2.2, J2.5, J2.6, J2.7, J2.SH, J3.2, J3.5, J3.6, J3.7, J3.SH, J5.1, R2.2, U1.3 (GND), U1.8 (GND), U1.13 (GND), U1.18 (GND), U1.23 (GND), U1.28 (GND), U1.33 (GND), U1.38 (GND), U1.42 (GND), U2.2 (GND), U3.7 (GND), U3.9, U3.11, U3.13, U4.1, U4.C1 (COMMON), U7.2 (GND)
unnamed: C5.1, R3.2, U3.1
unnamed: C6.1, R4.2, U3.3
unnamed: C7.1, R18.2, U3.5
unnamed: R15.2, R18.1, U4.2
unnamed: R3.1, R17.2, U4.A1 (CHANNEL_A)
unnamed: R4.1, R16.2, U4.B1 (CHANNEL_B)
unnamed: R1.2, R2.1, U5.1 (ADJ)
RES: J1.15, R9.2, U1.20 (GP15)
SCL0: D4.2 (A2), J2.4, R6.2, TP12.1 (1_1), U1.2 (GP1)
SCL1: D7.2 (A2), J3.4, R8.2, TP8.1 (1_1), U1.5 (GP3)
SCLK: J1.4, U1.14 (GP10)
SDA0: D4.1 (A1), J2.3, R5.2, TP13.1 (1_1), U1.1 (GP0)
SDA1: D7.1 (A1), J3.3, R7.2, TP9.1 (1_1), U1.4 (GP2)
SDIN: J1.5, U1.15 (GP11)
SENSE0: D8.2 (A2), J2.8, R13.2, TP11.1 (1_1), U1.6 (GP4)
SENSE1: D9.2 (A2), J3.8, R14.2, TP7.1 (1_1), U1.7 (GP5)
VCC: D5.2 (A), J5.2

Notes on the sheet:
ENCODER DEBOUNCE: RC filter + 74HC14 Schmitt inverter, one stage per contact (A, B, SW). 10k pulls the contact up to 3V3; R2 10k and C 10n form a 100 us low-pass that swallows contact bounce. The slow RC ramp would cross a plain logic threshold several times; the 74HC14's ~0.9 V hysteresis turns it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

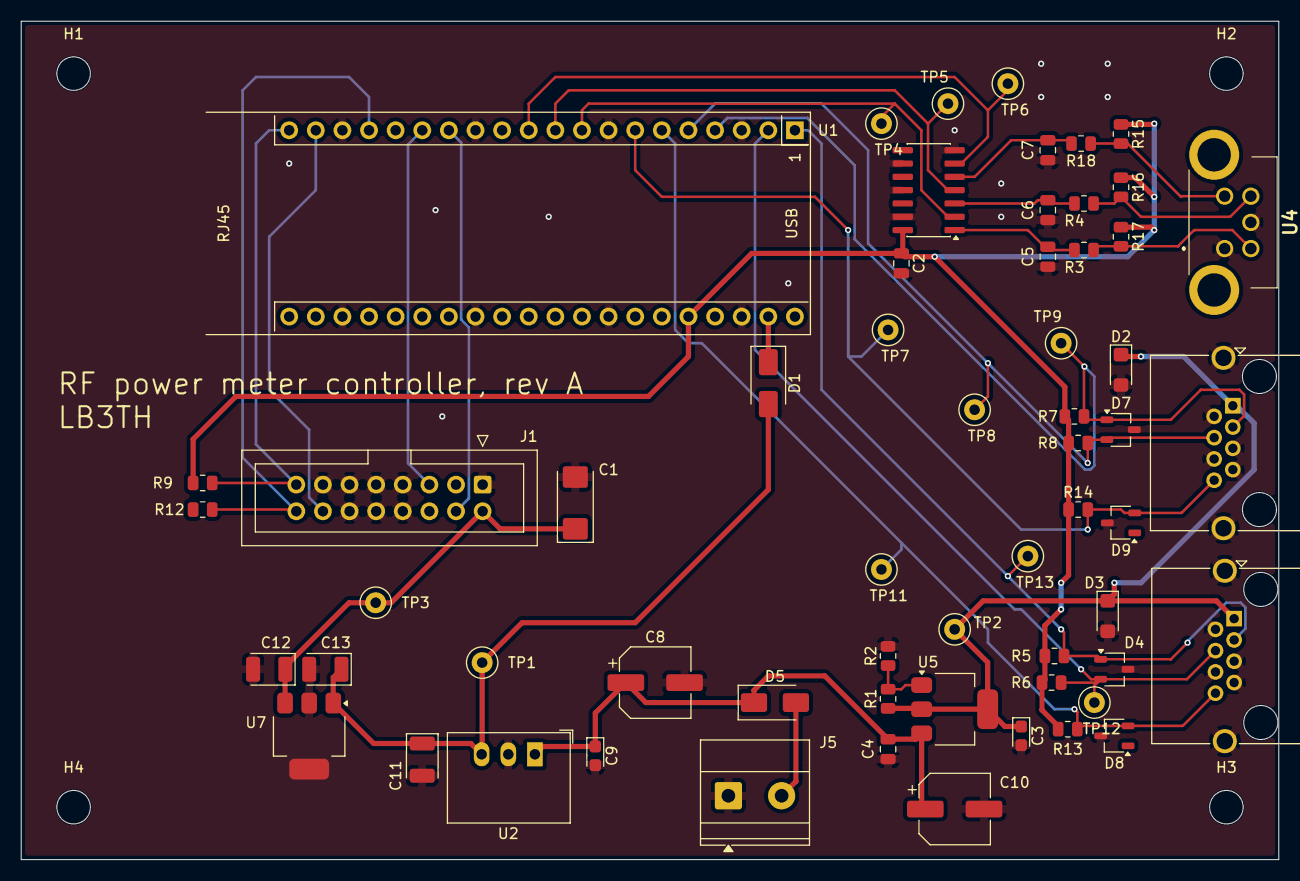
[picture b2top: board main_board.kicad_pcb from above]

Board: 2 copper layers, 120.0 x 80.0 mm, 63 parts (0 on the bottom side), 29 nets.

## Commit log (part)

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2025-12-24 First cut at software, after a bit of vibe-coding with Claude Code (Opus).
2025-12-25 Added an explanation for double ADCs.
2025-12-25 Added 3.3V to a 'presence pin' do detect hot-swapping of sensor heads.
2025-12-25 Add I2C and presence detect protection to hardware notes
    - I2C lines: TVS protection (PESD5V0L2BT-Q) for SDA/SCL
    - Presence detect: 10kΩ external pull-down + TVS protection
    - Summary table of all ESD protection components per RJ45
2025-12-25 Add I2C pull-up resistor recommendations
    - Main bus: 2.2kΩ pull-ups near Pico
    - Mux outputs: 10kΩ to keep lines defined when no sensor
    - Sensor module: 4.7kΩ to handle cable capacitance
2025-12-25 Add sensor module ESD protection and update component list
    - Add PESD5V0L2BT-Q for I2C lines on sensor module
    - Update sensor module component list with TVS and pull-ups
2025-12-25 Fix sensor module I2C schematic diagram
    Corrected ASCII art to show pull-ups from SDA/SCL to 3.3V,
    not in series with the signal path.
2025-12-26 Add TCA9548A configuration (address pins, reset, unused channels)
    - Address pins A0-A2 tied to GND for 0x70
    - RESET connected to GP4 with 10kΩ pull-up for bus recovery
    - Document that unused channels should be left floating (not grounded)
    - Update main schematic, pin assignments, and config.py
2025-12-26 Add ADS1115 ADDR pin configuration
    - ADS1115 #1: ADDR to GND for address 0x48
    - ADS1115 #2: ADDR to VDD for address 0x49
2025-12-27 Add ADS1115 ALERT/RDY pin configuration
    Pull-up to 3.3V via 10kΩ - not connected to GPIO since software uses polling.
2025-12-28 Change TVS diode from PESD5V0L2BT-Q to ESDAVLC6-2BLY
    ST part with lower capacitance (~0.45pF vs ~1pF) and better availability.
2025-12-28 Started schematics and layout. Not finished!
